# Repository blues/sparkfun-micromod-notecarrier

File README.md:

# Sparkfun Micromod Function Card Notecarrier

These are the the design files for the Sparkfun Micromod function board.

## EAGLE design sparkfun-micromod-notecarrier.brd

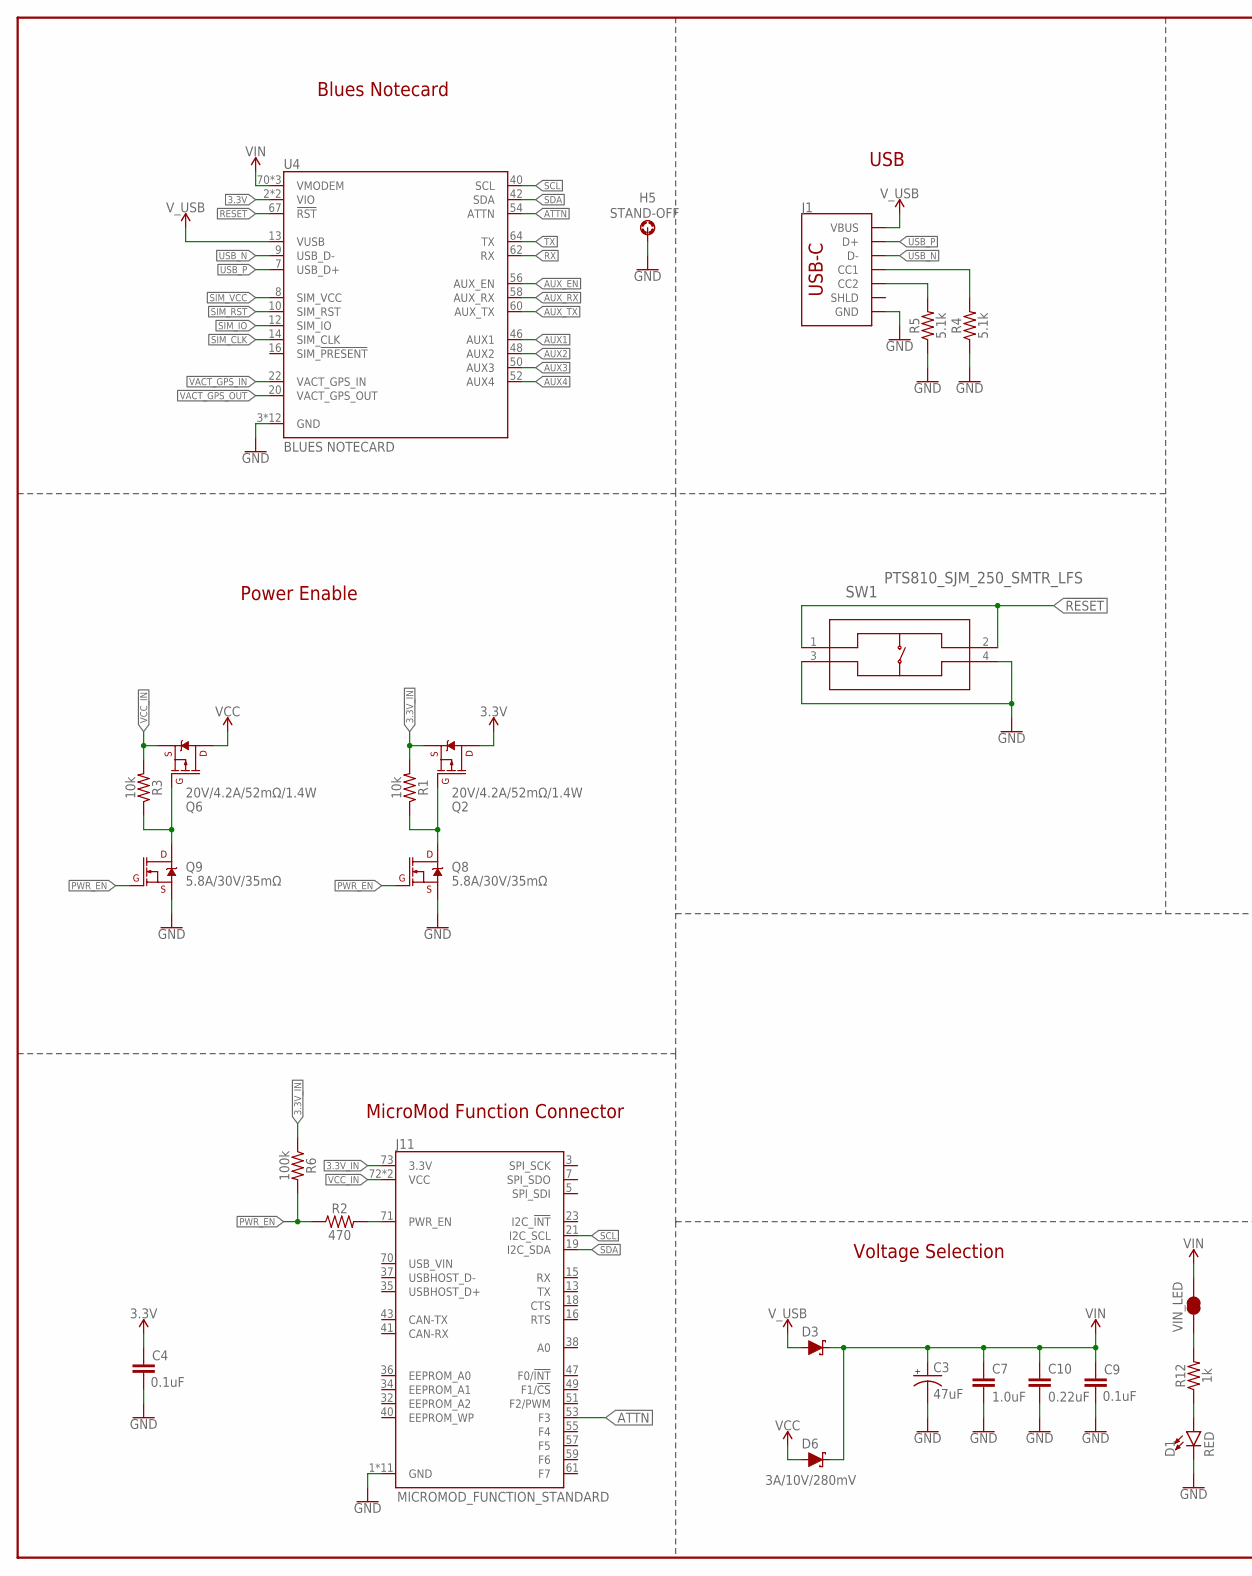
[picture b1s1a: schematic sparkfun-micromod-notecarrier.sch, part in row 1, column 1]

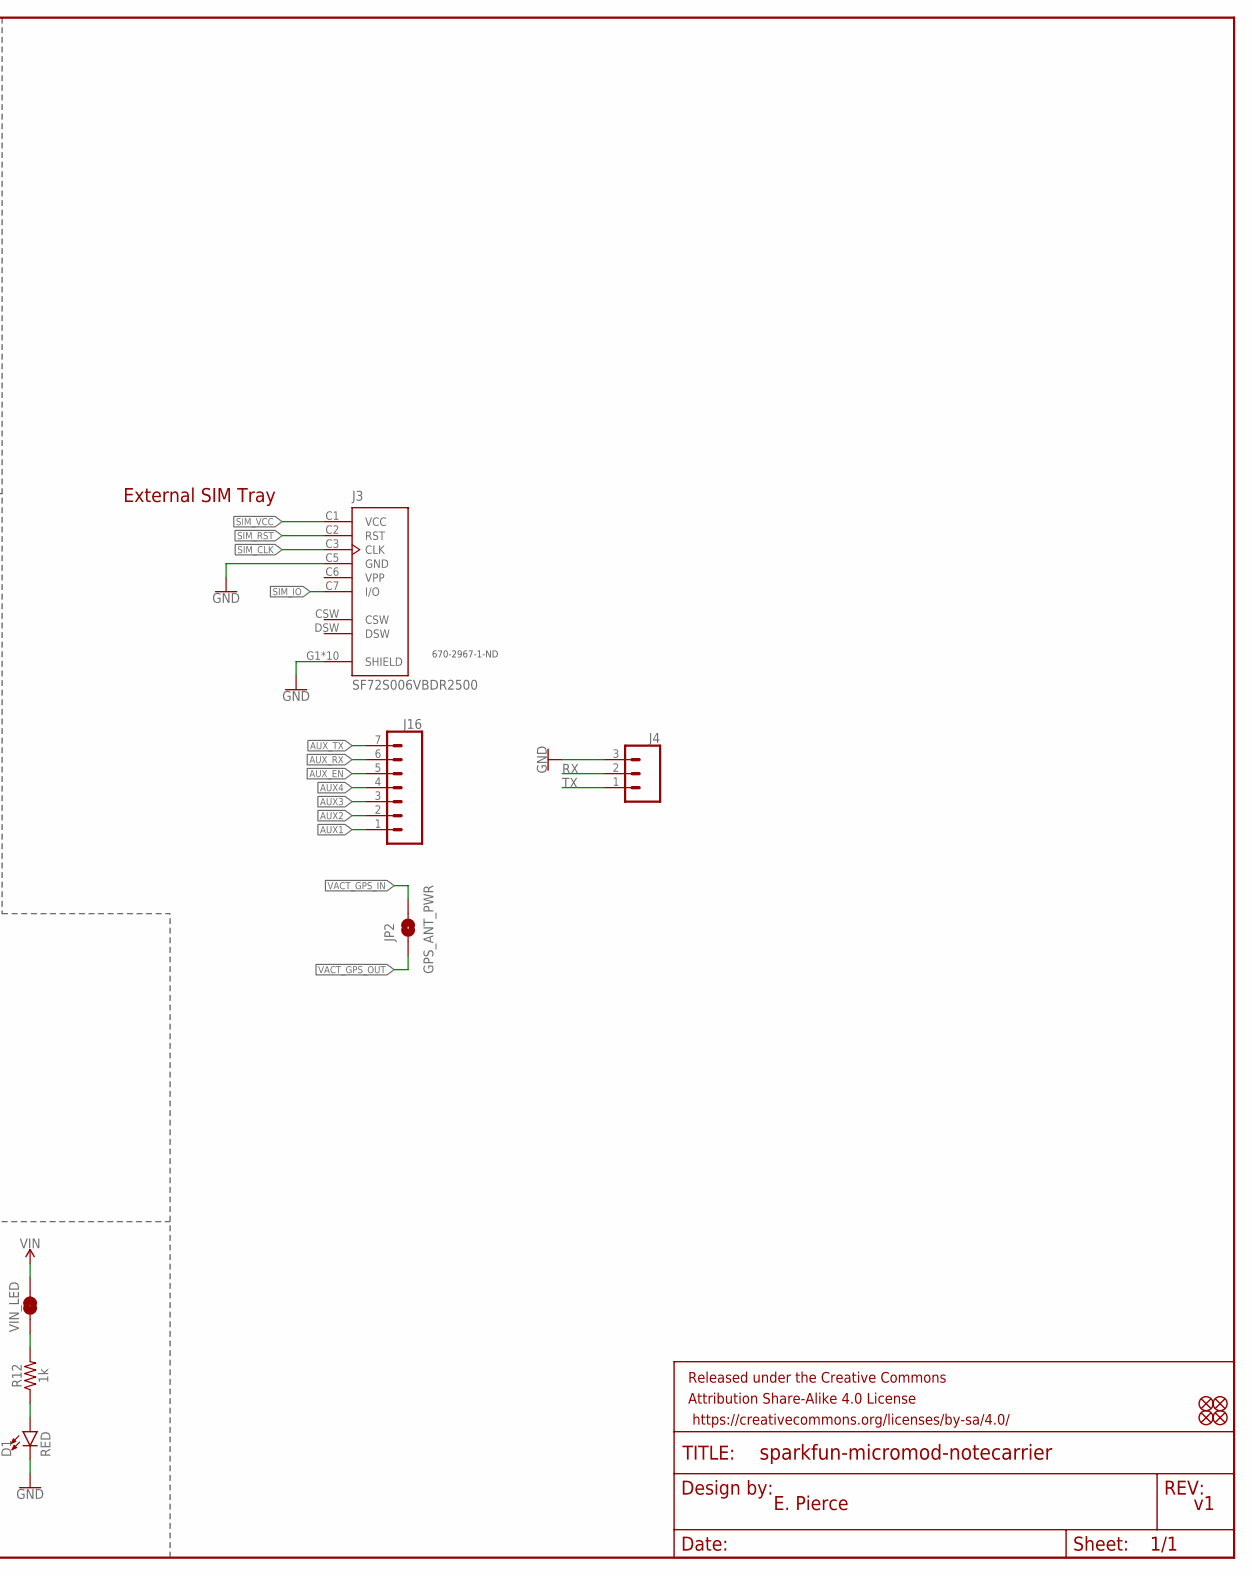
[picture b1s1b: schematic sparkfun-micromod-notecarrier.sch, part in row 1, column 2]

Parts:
C3: 47uF; EIA3528
C4, C9: 0.1uF; 0603
C7: 1.0uF; 0603
C10: 0.22uF; 0603
D1: RED; LED-0603
D3, D6: 3A/10V/280mV; SOD-323
FD1, FD2, FD3, FD4: FIDUCIALUFIDUCIAL; FIDUCIAL-MICRO
FRAME1: FRAME-LEDGER; CREATIVE_COMMONS
H5: STAND-OFF; STAND-OFF-REFLOW-M2.5
J1: USB_C_2-LAYER_PADS; USB-C-16P-2LAYER-PADS
J3: SF72S006VBDR2500; JAE_SF72S006VBDR2500
J4: CONN_031X03_NO_SILK; 1X03_NO_SILK
J11: MICROMOD_FUNCTION_STANDARD; M.2-CARD-E-22_FUNCTION_STANDARD
J16: CONN_07NO_SILK; 1X07_NO_SILK
JP2: GPS_ANT_PWR; SMT-JUMPER_2_NO_SILK
Q2, Q6: 20V/4.2A/52mΩ/1.4W; SOT23-3
Q8, Q9: 5.8A/30V/35mΩ; SOT23-3
R1, R3: 10k; 0603@1
R2: 470; 0603@1
R4, R5: 5.1k; 0603
R6: 100k; 0603@1
R12: 1k; 0603
SW1: PTS810_SJM_250_SMTR_LFS; PTS810_CNK
U4: BLUES NOTECARD; M.2-CONNECTOR-E
VIN_LED: JUMPER-SMT_2_NC_TRACE_SILK; SMT-JUMPER_2_NC_TRACE_SILK

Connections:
3.3V: C4.1, Q2.3 (D), U4.2 (VIO), U4.4 (VIO)
3.3V_IN: J11.73 (3.3V), Q2.2 (S), R1.2, R6.1
!RESET!: SW1.1, SW1.2, U4.67 (!RST!)
ATTN: J11.53 (F3), U4.54 (ATTN)
AUX1: J16.1, U4.46 (AUX1)
AUX2: J16.2, U4.48 (AUX2)
AUX3: J16.3, U4.50 (AUX3)
AUX4: J16.4, U4.52 (AUX4)
AUX_EN: J16.5, U4.56 (AUX_EN)
AUX_RX: J16.6, U4.58 (AUX_RX)
AUX_TX: J16.7, U4.60 (AUX_TX)
GND: C3.C (-), C4.2, C7.2, C9.2, C10.2, D1.C, H5.1, J1.GND, J1.GND2 (GND), J3.C5 (GND), J3.G1 (SHIELD), J3.G2 (SHIELD), J3.G3 (SHIELD), J3.G4 (SHIELD), J3.G5 (SHIELD), J3.G6 (SHIELD), J3.G7 (SHIELD), J3.G8 (SHIELD), J3.G9 (SHIELD), J3.G10 (SHIELD), J4.3, J11.1 (GND), J11.33 (GND), J11.39 (GND), J11.45 (GND), J11.75 (GND), J11.GND1 (GND), J11.GND2 (GND), J11.GND3 (GND), J11.GND4 (GND), J11.GND5 (GND), J11.GND6 (GND), Q8.2 (S), Q9.2 (S), R4.1, R5.1, SW1.3, SW1.4, U4.3 (GND), U4.5 (GND), U4.6 (GND), U4.11 (GND), U4.18 (GND), U4.33 (GND), U4.39 (GND), U4.45 (GND), U4.51 (GND), U4.57 (GND), U4.71 (GND), U4.73 (GND)
unnamed: Q2.1 (G), Q8.3 (D), R1.1
unnamed: Q6.1 (G), Q9.3 (D), R3.1
unnamed: J11.71 (PWR_EN), R2.2
unnamed: J1.A5 (CC1), R4.2
unnamed: J1.B5 (CC2), R5.2
unnamed: R12.2, VIN_LED.1
unnamed: D1.A, R12.1
PWR_EN: Q8.1 (G), Q9.1 (G), R2.1, R6.2
RX: J4.2, U4.62 (RX)
SCL: J11.21 (I2C_SCL), U4.40 (SCL)
SDA: J11.19 (I2C_SDA), U4.42 (SDA)
SIM_CLK: J3.C3 (CLK), U4.14 (SIM_CLK)
SIM_IO: J3.C7 (I/O), U4.12 (SIM_IO)
SIM_RST: J3.C2 (RST), U4.10 (SIM_RST)
SIM_VCC: J3.C1 (VCC), U4.8 (SIM_VCC)
TX: J4.1, U4.64 (TX)
USB_N: J1.A7 (D-), J1.B7 (D-), U4.9 (USB_D-)
USB_P: J1.A6 (D+), J1.B6 (D+), U4.7 (USB_D+)
VACT_GPS_IN: JP2.2, U4.22 (VACT_GPS_IN)
VACT_GPS_OUT: JP2.1, U4.20 (VACT_GPS_OUT)
VCC: D6.A, Q6.3 (D)
VCC_IN: J11.72 (VCC), J11.74 (VCC), Q6.2 (S), R3.2
VIN: C3.A (+), C7.1, C9.1, C10.1, D3.C, D6.C, U4.70 (VMODEM), U4.72 (VMODEM), U4.74 (VMODEM), VIN_LED.2
VPP: J3.C6 (VPP)
V_USB: D3.A, J1.VBUS1 (VBUS), J1.VBUS2 (VBUS), U4.13 (VUSB)

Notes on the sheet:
MicroMod Function Connector
E. Pierce
Power Enable
USB
Voltage Selection
670-2967-1-ND
Blues Notecard
External SIM Tray

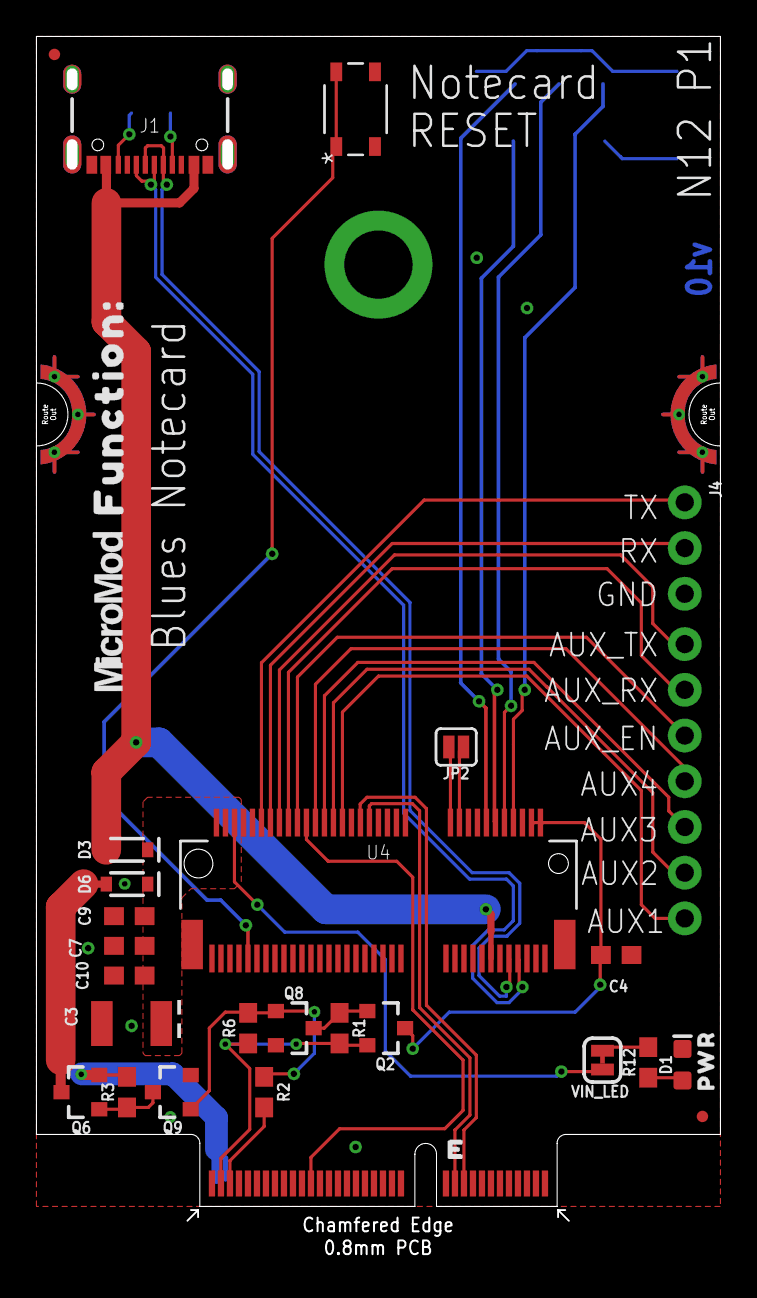
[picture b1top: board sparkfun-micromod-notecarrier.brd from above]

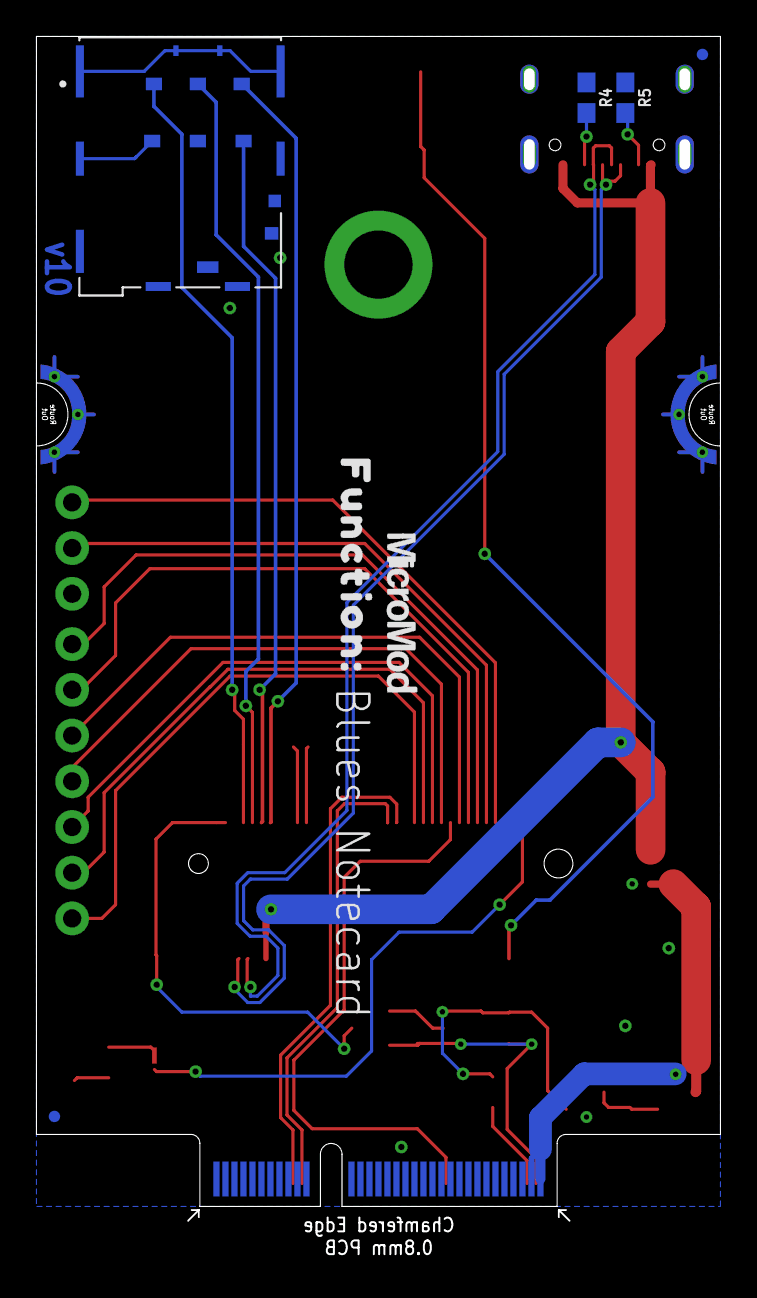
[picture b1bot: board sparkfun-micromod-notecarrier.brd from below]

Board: 2 copper layers, 37.5 x 67.5 mm, 40 parts (7 on the bottom side), 36 nets.

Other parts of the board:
LOGO2: SPECIAL_INSTRUCTIONS-ORDERING; ORDERING_INSTRUCTIONS
U$4, U$8: FUNCTION#0
U$7: PWR0
U$37, U$63: MICROMOD_LOGO_.35

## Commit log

2022-05-02 added design files
2022-05-02 added picture

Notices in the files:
parts and their libraries:
SparkFun-Aesthetics: Licensing: Creative Commons ShareAlike 4.0 International - https://creativecommons.org/licenses/by-sa/4.0
SparkFun-Aesthetics: Released under the Creative Commons Attribution Share-Alike 4.0 License
SparkFun-Aesthetics: https://creativecommons.org/licenses/by-sa/4.0
